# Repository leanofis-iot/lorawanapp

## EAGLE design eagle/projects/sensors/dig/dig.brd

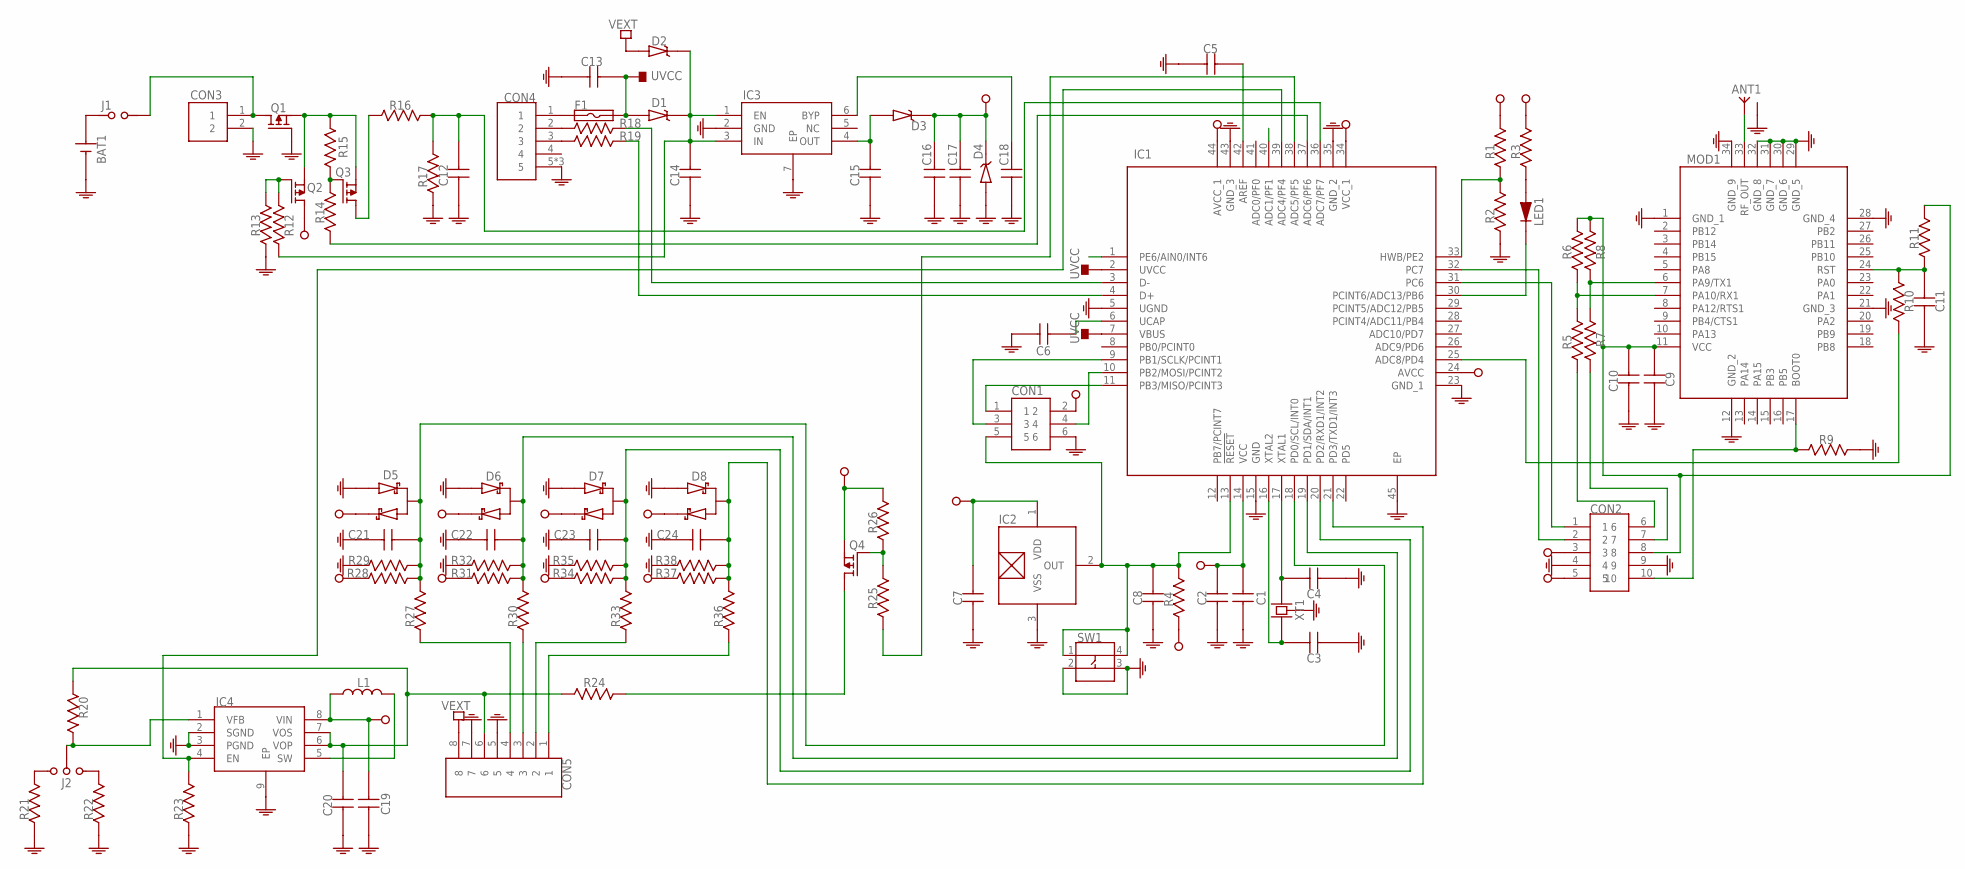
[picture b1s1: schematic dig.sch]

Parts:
ANT1: SMA-RF
BAT1: 211P-C-HOLDER
C1, C2, C3, C4, C5, C6, C7, C8, C9, C10, C11, C12, C13, C16, C17, C18, C21, C22, C23, C24: CAPACITOR-0603; 0603
C14, C15, C19, C20: CAPACITOR-0805; 0805
CON1: ISP
CON2: HEADER-10P-2R-DIP-2_54MM
CON3: JST-PH-2-2.0MM
CON4: USB-MICRO-DIP-VER
CON5: CON-3_50MM-8P-1985250
D1, D2, D3: DIODE-SCHOTTKY; SOD123-DIODE
D4: ZENER-SOD123; SOD123-DIODE
D5, D6, D7, D8: SCHOTTKY-SERIE-3P; SOT23-3
F1: FUSE-1206; 1206
IC1: ATMEGA32U4-MU; QFN-44
IC2: S-5712-SOT23-3; SOT23-3
IC3: MIC5219-VDFN-6; VDFN-6
IC4: MCP1640-DFN-8; DFN-8-2X3
J1: JUMPER; HEADER-2P-DIP-2_54MM
J2: JUMPER-3P; HEADER-3P-DIP-2_54MM
L1: INDUCTOR-0520-0630
LED1: LED-0603
MOD1: RAK811
Q1, Q2, Q3, Q4: P-MOSFET; SOT23-3
R1, R2, R3, R4, R5, R6, R7, R8, R9, R10, R11, R12, R13, R14, R15, R16, R17, R18, R19, R20, R21, R22, R23, R24, R25, R26: RESISTOR-0603; 0603
R27, R30, R33, R36: RESISTOR-0805; 0805
R28, R29, R31, R32, R34, R35, R37, R38: RESISTOR-JMP-2_54MM; HEADER-2P-DIP-2_54MM
SW1: BUTTON-4P-SMD-5X5
XT1: CRYSTAL-5032-4P

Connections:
GND: ANT1.2 (GND), ANT1.3 (GND), ANT1.4 (GND), ANT1.5 (GND), BAT1.2 (-), C1.1, C2.1, C3.1, C4.1, C5.1, C6.1, C7.1, C8.1, C9.1, C10.1, C11.1, C12.1, C13.1, C14.1, C15.1, C16.1, C17.1, C18.1, C19.1, C20.1, C21.1, C22.1, C23.1, C24.1, CON1.6, CON2.4, CON2.9, CON3.2, CON4.5, CON4.6 (5), CON4.7 (5), CON5.5, CON5.7, D4.2 (A), D5.1, D6.1, D7.1, D8.1, IC1.5 (UGND), IC1.15 (GND), IC1.23 (GND_1), IC1.35 (GND_2), IC1.43 (GND_3), IC1.45 (EP), IC2.3 (VSS), IC3.2 (GND), IC3.7 (EP), IC4.2 (SGND), IC4.3 (PGND), IC4.9 (EP), MOD1.1 (GND_1), MOD1.12 (GND_2), MOD1.21 (GND_3), MOD1.28 (GND_4), MOD1.29 (GND_5), MOD1.30 (GND_6), MOD1.31 (GND_7), MOD1.32 (GND_8), MOD1.34 (GND_9), Q1.1 (G), R2.1, R9.2, R13.1, R17.1, R21.1, R22.1, R23.1, R29.1, R32.1, R35.1, R38.1, SW1.2, SW1.3, XT1.2 (GND), XT1.4 (GND)
unnamed: C11.2, MOD1.24 (RST), R10.1, R11.1
unnamed: CON1.1, IC1.11 (PB3/MISO/PCINT3)
unnamed: ANT1.1 (ANT), MOD1.33 (RF_OUT)
unnamed: CON5.4, R27.1
unnamed: MOD1.7 (PA10/RX1), R5.2, R6.1
unnamed: MOD1.6 (PA9/TX1), R7.2, R8.1
unnamed: CON4.1, F1.1
unnamed: CON1.4, IC1.10 (PB2/MOSI/PCINT2)
unnamed: C3.2, IC1.16 (XTAL2), XT1.1
unnamed: CON2.1, IC1.31 (PC6)
unnamed: C4.2, IC1.17 (XTAL1), XT1.3 (2)
unnamed: C9.2, C10.2, CON2.8, MOD1.11 (VCC), R6.2, R8.2, R11.2
unnamed: CON2.7, R7.1
unnamed: C20.2, CON5.6, IC4.6 (VOP), IC4.7 (VOS), R20.1, R24.2
unnamed: IC1.25 (ADC8/PD4), R10.2
unnamed: IC1.30 (PCINT6/ADC13/PB6), LED1.1 (K)
unnamed: CON5.2, R33.1
unnamed: CON5.3, R30.1
unnamed: IC4.1 (VFB), J2.2, R20.2
unnamed: CON5.1, R36.1
unnamed: Q4.3 (D), R24.1
unnamed: CON2.2, IC1.32 (PC7)
unnamed: C5.2, IC1.42 (AREF)
unnamed: Q3.1 (G), R14.2, R15.2
unnamed: C6.2, IC1.6 (UCAP)
unnamed: LED1.2 (A), R3.1
unnamed: C12.2, IC1.36 (ADC7/PF7), R16.2, R17.2
unnamed: C18.2, IC3.6 (BYP)
unnamed: C14.2, D1.1 (K), D2.1 (K), IC3.1 (EN), IC3.3 (IN), R12.1
unnamed: J2.1, R22.2
unnamed: C15.2, D3.2 (A), IC3.4 (OUT)
unnamed: CON4.2, R18.1
unnamed: CON4.3, R19.1
unnamed: IC1.3 (D-), R18.2
unnamed: IC1.4 (D+), R19.2
unnamed: CON1.3, IC1.9 (PB1/SCLK/PCINT1)
unnamed: Q4.1 (G), R25.2, R26.1
unnamed: IC1.37 (ADC6/PF6), R14.1
unnamed: J2.3, R21.2
unnamed: IC1.38 (ADC5/PF5), R25.1
unnamed: BAT1.1 (+), J1.1
unnamed: C21.2, D5.3, IC1.18 (PD0/SCL/INT0), R27.2, R28.2, R29.2
unnamed: Q2.1 (G), R12.2, R13.2
unnamed: C22.2, D6.3, IC1.19 (PD1/SDA/INT1), R30.2, R31.2, R32.2
unnamed: CON3.1, J1.2 (3), Q1.3 (D)
unnamed: C23.2, D7.3, IC1.20 (PD2/RXD1/INT2), R33.2, R34.2, R35.2
unnamed: Q1.2 (S), Q2.2 (S), Q3.2 (S), R15.1
unnamed: Q3.3 (D), R16.1
unnamed: CON2.6, R5.1
unnamed: IC1.33 (HWB/PE2), R1.1, R2.2
unnamed: C24.2, D8.3, IC1.21 (PD3/TXD1/INT3), R36.2, R37.2, R38.2
unnamed: CON2.10, MOD1.17 (BOOT0), R9.1
unnamed: C8.2, CON1.5, IC1.13 (!RESET), IC2.2 (OUT), R4.2, SW1.1, SW1.4
unnamed: IC4.5 (SW), L1.2
unnamed: IC1.39 (ADC4/PF4), IC4.4 (EN), R23.2
UVCC: C13.2, D1.2 (A), F1.2, IC1.2 (UVCC), IC1.7 (VBUS)
VCC: C1.2, C2.2, C7.2, C16.2, C17.2, C19.2, CON1.2, CON2.3, CON2.5, D3.1 (K), D4.1 (K), D5.2, D6.2, D7.2, D8.2, IC1.14 (VCC), IC1.24 (AVCC), IC1.34 (VCC_1), IC1.44 (AVCC_1), IC2.1 (VDD), IC4.8 (VIN), L1.1, Q2.3 (D), Q4.2 (S), R1.2, R3.2, R4.1, R26.2, R28.1, R31.1, R34.1, R37.1
VEXT: CON5.8, D2.2 (A)

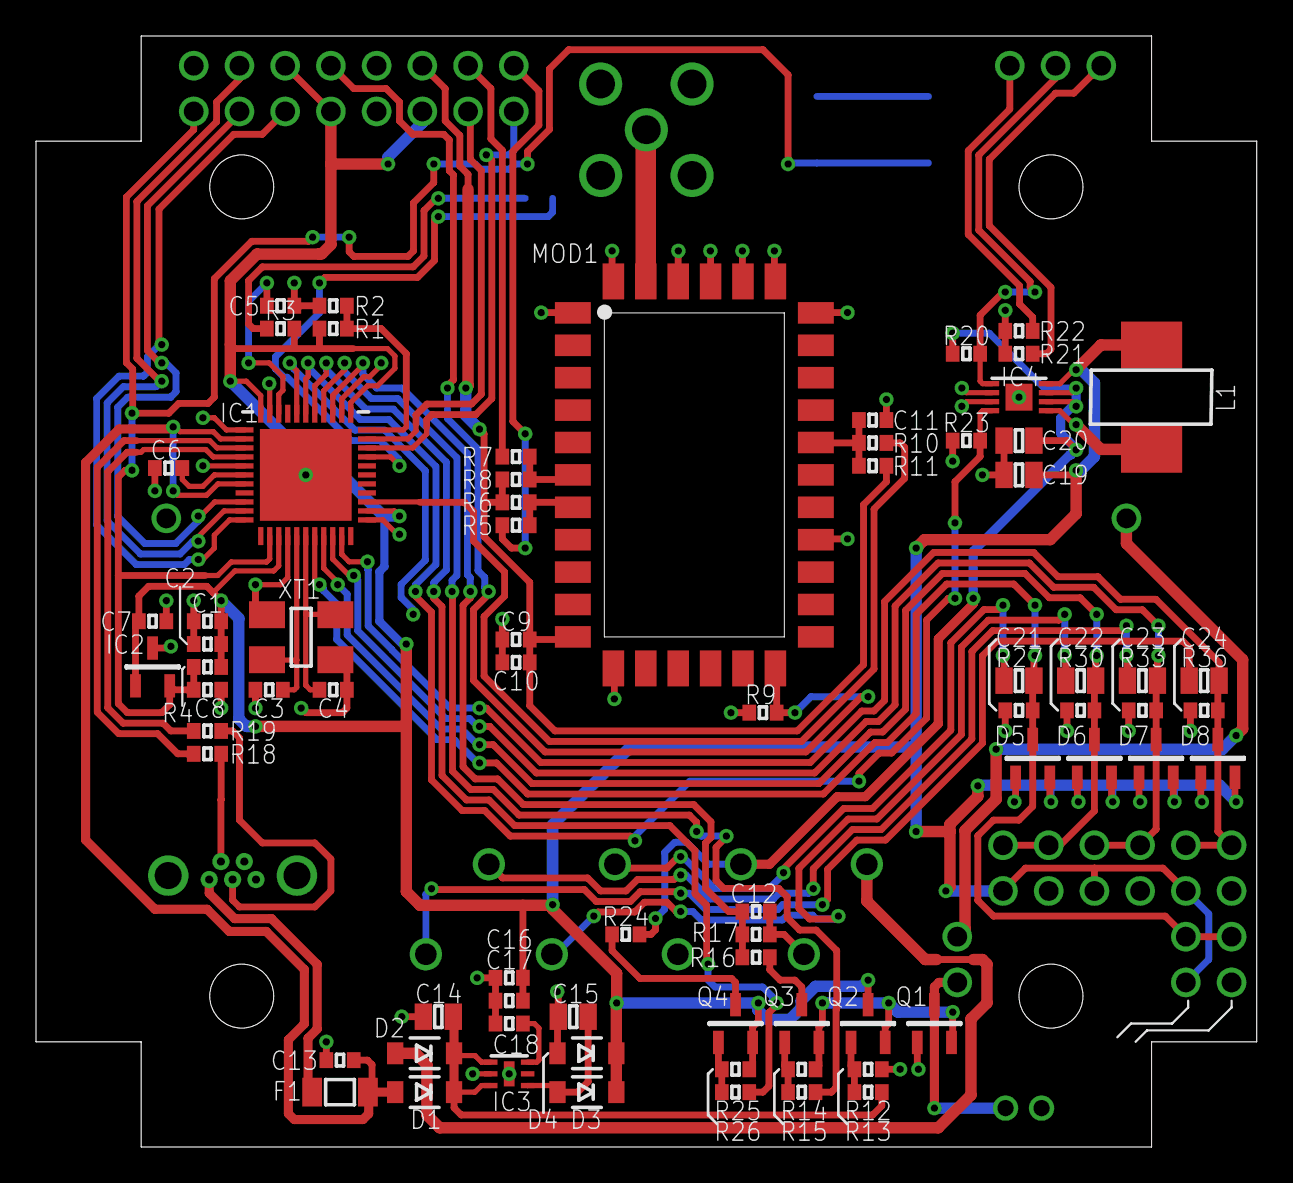
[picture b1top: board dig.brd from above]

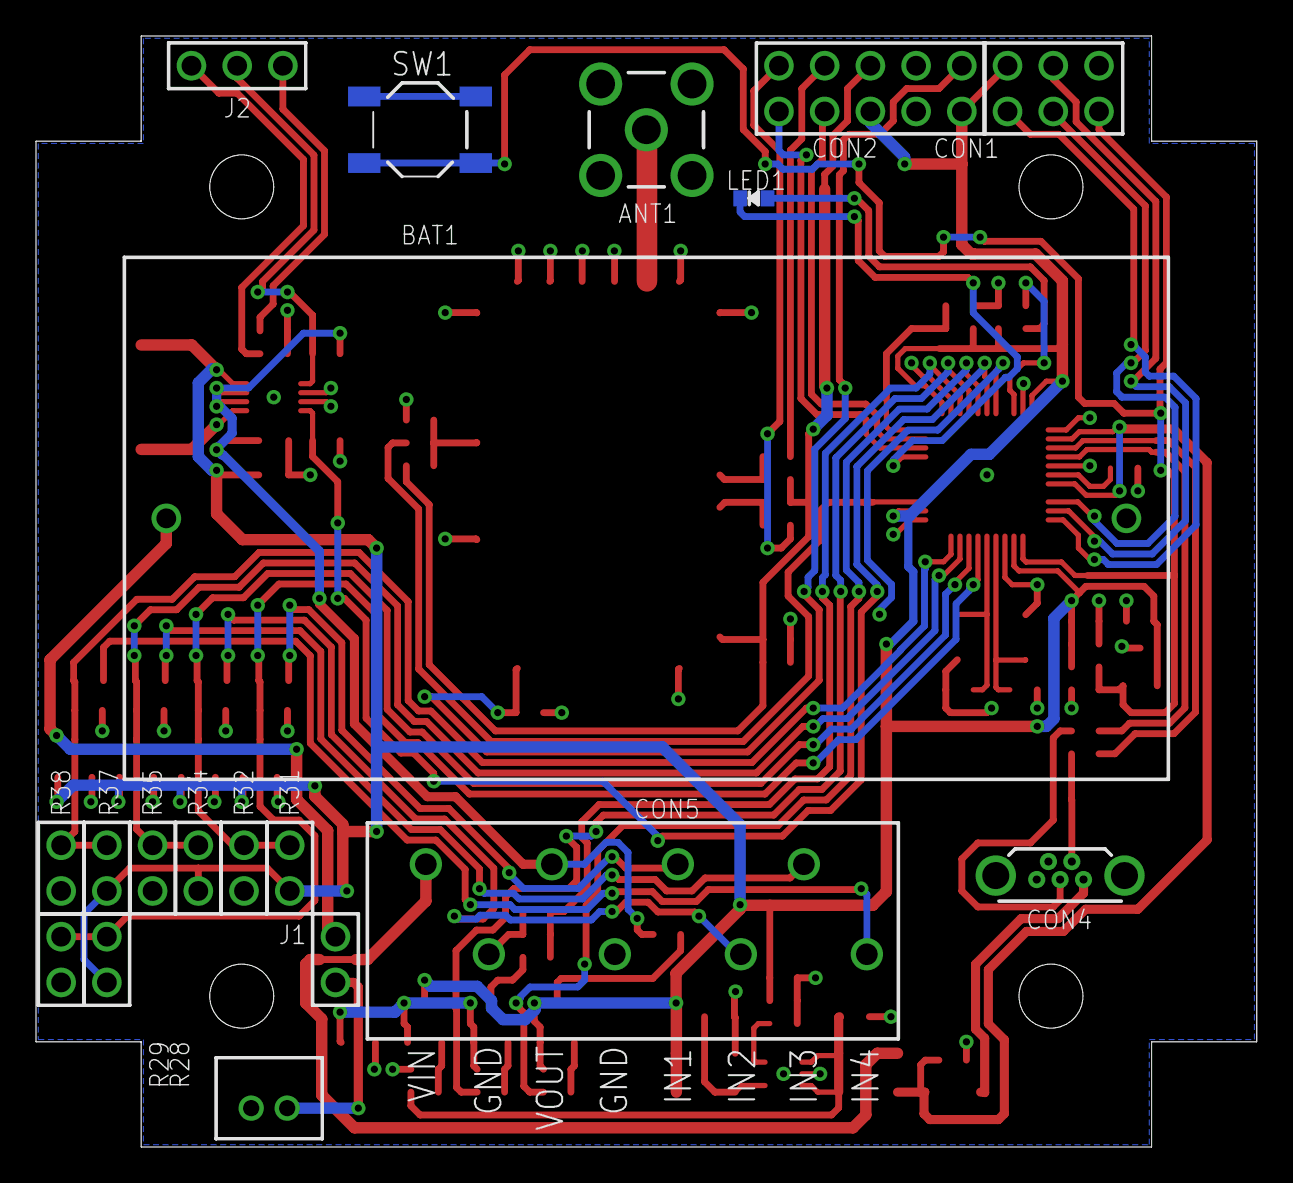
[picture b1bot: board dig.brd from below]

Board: 2 copper layers, 67.8 x 61.7 mm, 93 parts (19 on the bottom side), 59 nets.

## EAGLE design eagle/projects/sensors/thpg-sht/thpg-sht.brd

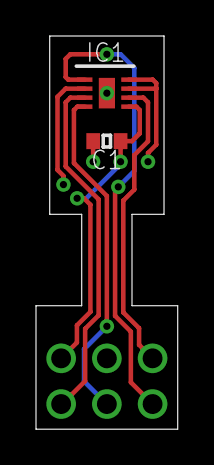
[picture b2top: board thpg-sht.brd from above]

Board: 2 copper layers, 7.9 x 21.8 mm, 3 parts (1 on the bottom side), 6 nets.

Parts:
C1: 0603
CON1: HEADER-6P-2R-DIP-2_54MM
IC1: SHT3X-DIS

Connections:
GND: C1.1, CON1.2, IC1.2, IC1.7, IC1.8, IC1.9
unnamed: CON1.3, IC1.6
unnamed: CON1.6, IC1.1
unnamed: CON1.5, IC1.4
unnamed: CON1.4, IC1.3
VCC: C1.2, CON1.1, IC1.5

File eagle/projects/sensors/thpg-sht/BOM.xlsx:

IC1 | SHT31-DIS | DFN-8
CON1 | HEADER 2.54MM 6P 2R | DIP
C1 | 100NF | 0603
PCB
